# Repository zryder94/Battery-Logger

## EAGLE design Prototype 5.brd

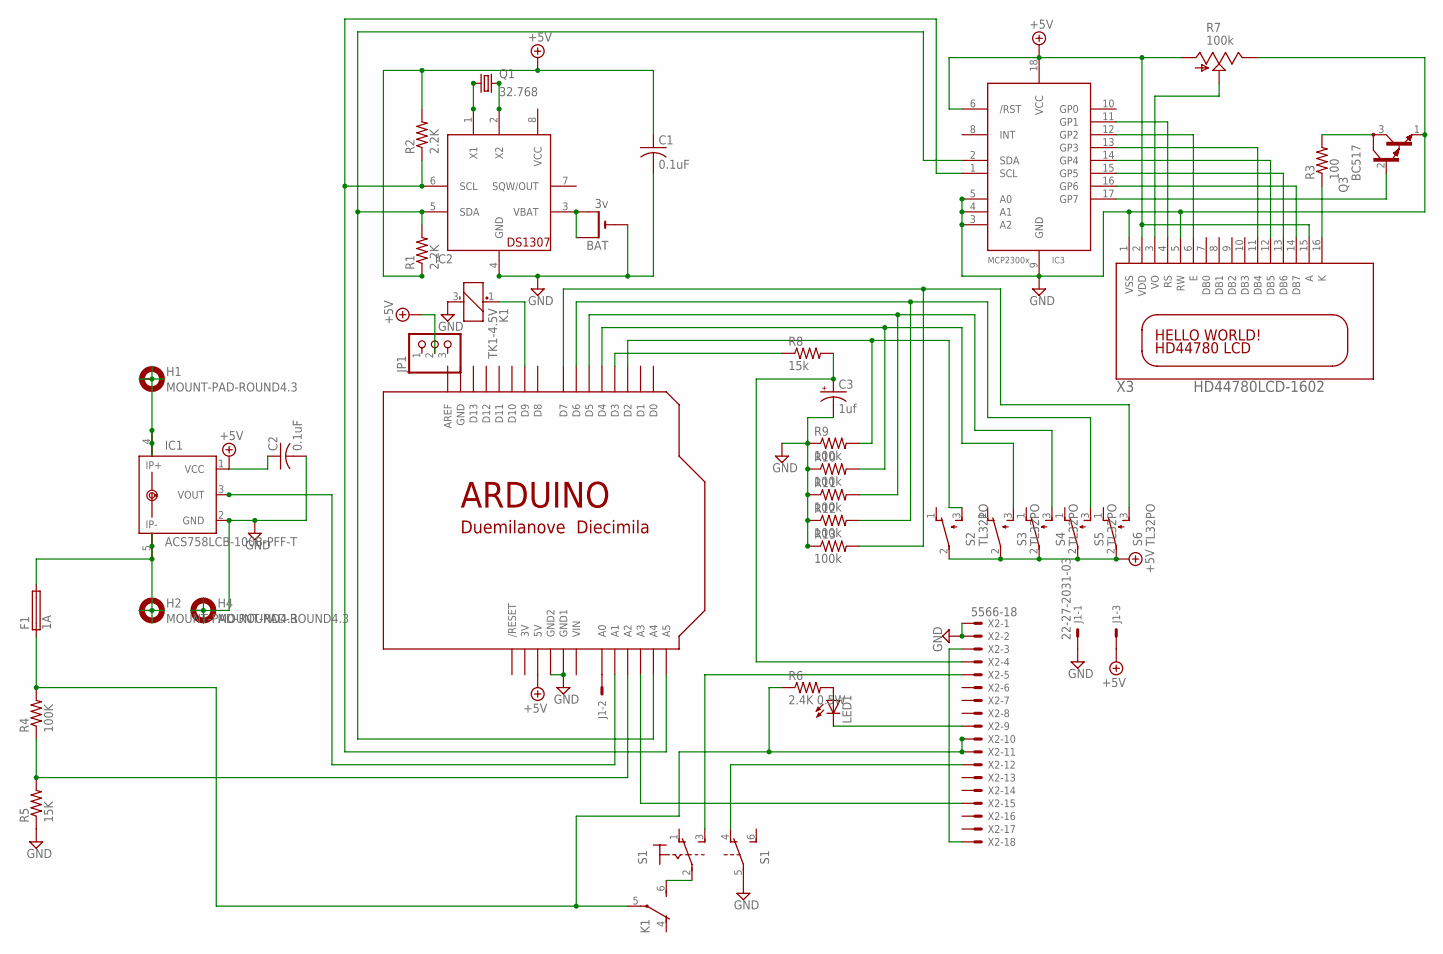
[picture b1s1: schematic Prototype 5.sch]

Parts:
BAT: 3v; CR1220-THM
C1, C2: 0.1uF; C050-024X044
C3: 1uf; E2,5-6E
F1: 1A; SH22,5
H1, H2, H4: MOUNT-PAD-ROUND4.3; 4,3-PAD
IC1: ACS758LCB-100B-PFF-T; CB-PFF
IC2: DS1307; DIL08
IC3: MCP2300X/P; DIL18
J1: 22-27-2031-03; 6410-03
JP1: PINHD-1X3; 1X03
K1: TK1-4.5V; TK
LED1: LED5MM
Q1: 32.768; TC38H
Q3: BC517; TO92
R1, R2: 2.2K; 0207/10
R3: 100; 0207/10
R4: 100K; 0207/10
R5: 15K; 0207/10
R6: 2.4K 0.5W; 0207/10
R7: 100k; B25U
R8: 15k; 0207/10
R9, R10, R11, R12, R13: 100k; 0207/10
S1: 320-938
S2, S3, S4, S5, S6: TL32PO; TL3XPO
U$1: ARDUINO-NOHOLE
X2: 5566-18
X3: HD44780LCD-1602; LCD1602

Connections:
3V: U$1.3V
24V: F1.2, H2.B4,3, IC1.5 (IP-), IC1.IP-1
+5V: C1.1, C2.1, IC1.1 (VCC), IC3.6 (/RST), IC3.18 (VCC), J1.3, JP1.2, R1.1, R2.2, R7.A, S2.2, S3.2, S4.2, S5.2, S6.2, U$1.5V, X3.2 (VDD), X3.15 (A)
GND: BAT.-, C1.2, C2.2, C3.-, H4.B4,3, IC1.2 (GND), IC2.4 (GND), IC3.3 (A2), IC3.4 (A1), IC3.5 (A0), IC3.9 (GND), J1.1, K1.3 (-), Q3.1 (E), R5.1, R7.E, R9.1, R10.1, R11.1, R12.1, R13.1, S1.5, U$1.GND, U$1.GND1, U$1.GND2, X2.1, X2.2, X3.1 (VSS), X3.5 (RW)
unnamed: IC2.1 (X1), Q1.1
unnamed: IC2.2 (X2), Q1.2
unnamed: C3.+, R8.2, X2.4
unnamed: BAT.+1 (+), BAT.+2 (+1), IC2.3 (VBAT)
unnamed: J1.2, U$1.A0
unnamed: IC1.3 (VOUT), U$1.A1
unnamed: IC2.6 (SCL), IC3.1 (SCL), R2.1, U$1.A5
unnamed: IC2.5 (SDA), IC3.2 (SDA), R1.2, U$1.A4
unnamed: H1.B4,3, IC1.4 (IP+), IC1.IP+1
unnamed: IC3.12 (GP2), X3.6 (E)
unnamed: IC3.11 (GP1), X3.4 (RS)
unnamed: R9.2, S2.3 (S), U$1.D2
unnamed: R10.2, S3.3 (S), U$1.D4
unnamed: S1.3 (S), X2.5
unnamed: K1.6 (S), S1.2
unnamed: LED1.K (C), X2.9
unnamed: R4.1, R5.2, U$1.A2
unnamed: S1.4 (O), X2.12
unnamed: K1.1 (+), U$1.D9
unnamed: R8.1, U$1.D3
unnamed: R13.2, S6.3 (S), U$1.D7
unnamed: IC3.17 (GP7), Q3.2 (B)
unnamed: IC3.13 (GP3), X3.11 (DB4)
unnamed: R3.1, X3.16 (K)
unnamed: Q3.3 (C), R3.2
unnamed: LED1.A, R6.2
unnamed: IC3.14 (GP4), X3.12 (DB5)
unnamed: U$1.A3, X2.15
unnamed: R11.2, S4.3 (S), U$1.D5
unnamed: X2.3, X2.18
unnamed: IC3.15 (GP5), X3.13 (DB6)
unnamed: F1.1, K1.5, R4.2, R6.1, X2.10, X2.11
unnamed: IC3.16 (GP6), X3.14 (DB7)
unnamed: R7.S, X3.3 (VO)
unnamed: R12.2, S5.3 (S), U$1.D6
VCC: IC2.8 (VCC)
VIN: U$1.VIN

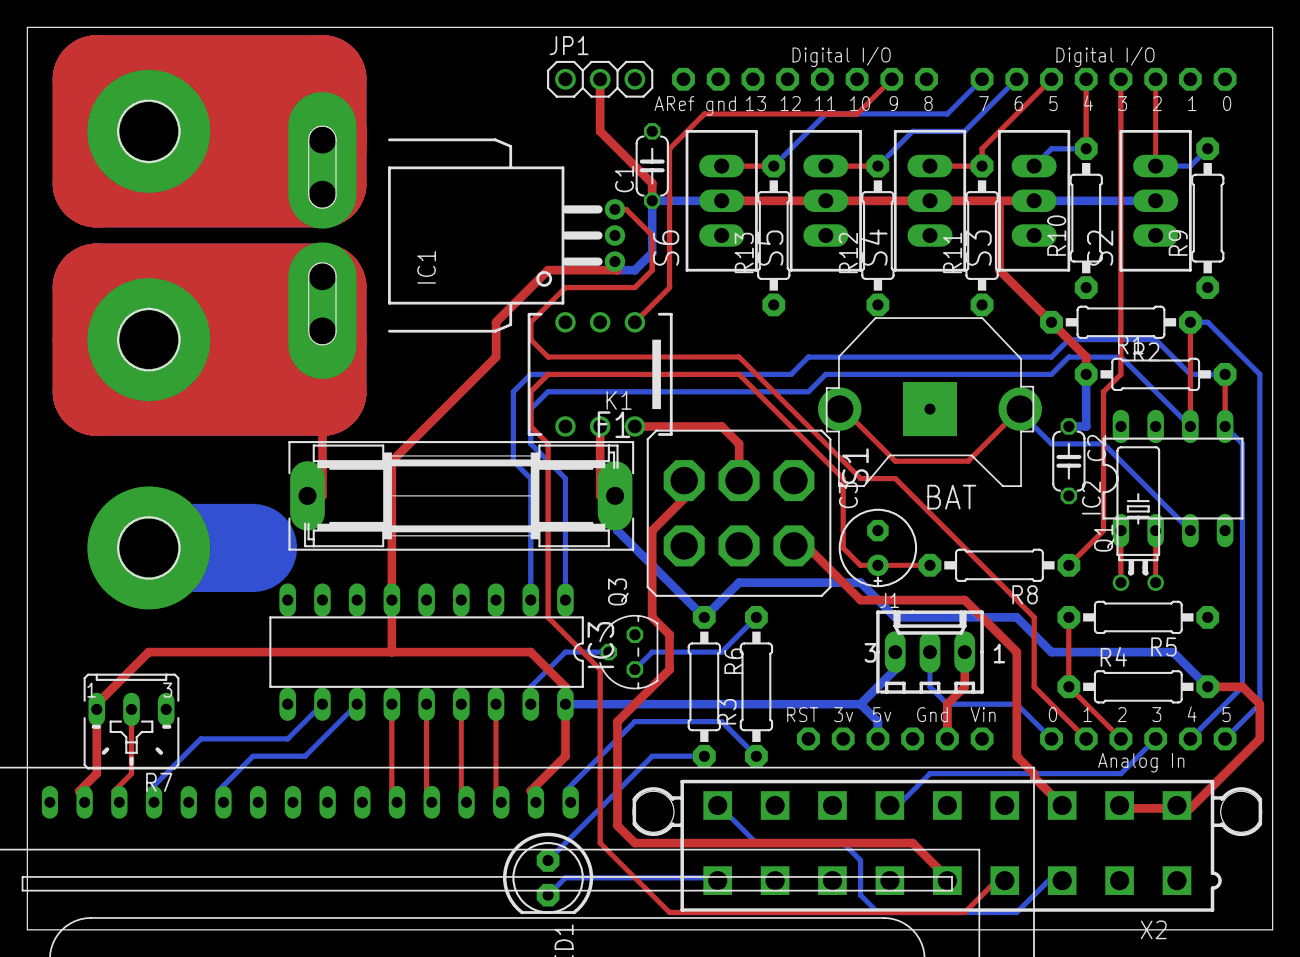
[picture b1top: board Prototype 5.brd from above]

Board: 2 copper layers, 91.1 x 66.0 mm, 39 parts (0 on the bottom side), 38 nets.

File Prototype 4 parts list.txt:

Partlist

Exported from Prototype 4.sch at 4/30/2012 8:23:52 AM

EAGLE Version 6.0.0 Copyright (c) 1988-2011 CadSoft

Assembly variant: 

Part     Value                Device               Package        Library        Sheet

BAT      3v                   CR1220THM            CR1220-THM     adafruit       1	3001K-ND
C1       0.1uF                C-US050-024X044      C050-024X044   adafruit       1	478-6008-ND
C2       0.1uF                C-US050-024X044      C050-024X044   adafruit       1	478-6008-ND
C3       1uf                  CPOL-USE2,5-6E       E2,5-6E        resistor       1	ECA-1HM010
F1       1A                   SH22,5               SH22,5         fuse           1	486-1258-ND
H1       MOUNT-PAD-ROUND4.3   MOUNT-PAD-ROUND4.3   4,3-PAD        holes          1
H2       MOUNT-PAD-ROUND4.3   MOUNT-PAD-ROUND4.3   4,3-PAD        holes          1
H4       MOUNT-PAD-ROUND4.3   MOUNT-PAD-ROUND4.3   4,3-PAD        holes          1
IC1      ACS758LCB-100B-PFF-T ACS758LCB-100B-PFF-T CB-PFF         allegro        1	620-1320-ND	40mV/A
IC2      DS1307               DS1307               DIL08          adafruit       1	DS1307+-ND
IC3      MCP2300X/P           MCP2300X/P           DIL18          adafruit       1	MCP23008-E/P-ND
J1       22-27-2031-03        22-27-2031-03        6410-03        con-molex      1	WM4201-ND
JP1                           PINHD-1X3            1X03           adafruit       1	A26509-40-ND
K1       TK1-4.5V             TK1-4.5V             TK             relay          1	255-1757-5-ND
LED1                          LED5MM               LED5MM         adafruit       1	C503B-RCN-CW0Z0AA1-ND
Q1       32.768               CRYSTALTC38H         TC38H          crystal        1	300-8763-ND
Q3       BC517                BC517                TO92           transistor-npn 1	BC517RL1GOSCT-ND
R1       2.2K                 R-US_0207/10         0207/10        adafruit       1	2.2KH-ND
R2       2.2K                 R-US_0207/10         0207/10        adafruit       1	2.2KH-ND
R3       100                  R-US_0207/10         0207/10        adafruit       1	100H-ND
R4       100K                 R-US_0207/10         0207/10        adafruit       1	100KADCT-ND
R5       15K                  R-US_0207/10         0207/10        adafruit       1	15KADCT-ND
R6       2.4K 0.5W            R-US_0207/10         0207/10        adafruit       1	2.4KH-ND
R7       100k                 TRIM_US-B25U         B25U           pot            1	3362U-104LF-ND
R8       15k                  R-US_0207/10         0207/10        adafruit       1	15KH-ND
R9       100k                 R-US_0207/10         0207/10        adafruit       1	100KH-ND
R10      100k                 R-US_0207/10         0207/10        adafruit       1	100KH-ND
R11      100k                 R-US_0207/10         0207/10        adafruit       1	100KH-ND
R12      100k                 R-US_0207/10         0207/10        adafruit       1	100KH-ND
R13      100k                 R-US_0207/10         0207/10        adafruit       1	100KH-ND
S1                            320-938              320-938        switch         1	A201P3ZQ04-ND
S2       TL32PO               TL32PO               TL3XPO         switch         1	SW630-ND
S3       TL32PO               TL32PO               TL3XPO         switch         1	SW630-ND
S4       TL32PO               TL32PO               TL3XPO         switch         1	SW630-ND
S5       TL32PO               TL32PO               TL3XPO         switch         1	SW630-ND
S6       TL32PO               TL32PO               TL3XPO         switch         1	SW630-ND
U$1      ARDUINO-NOHOLE       ARDUINO-NOHOLE       ARDUINO-NOHOLE adafruit       1
X2       5566-18              5566-18              5566-18        con-molex      1	WM3883-ND
X3       HD44780LCD-1602      HD44780LCD-1602      LCD1602        adafruitedit   1
				8 pin IC Socket						3M5473-ND
				18 pin IC Socket					3M5464-ND
				Resistor mounting kit					K3003-ND


5v non-latching relay 255-1028-5-ND
4.5v non-latching relay 255-1757-5-ND

pushbutton switches SW630-ND

Resistor mounting kit	K3003-ND


Index	Quantity	Part Number	Description	Customer Reference	Backorder Quantity	Unit Price	Extended Price
1	2	K3003-ND	MOUNTING KIT FOR FSE 1000		0	14.28000	$28.56
2	1	3001K-ND	HOLDER BATTERY COIN 12MM DIA THM		0	0.57000	$0.57
3	10	478-6008-ND	CAP CER 0.1UF 50V 5% RADIAL		0	0.41000	$4.10
4	2	P5174-ND	CAP ALUM 1UF 50V 20% RADIAL		0	0.20000	$0.40
5	1	486-1258-ND	FUSEHOLDER 22.5MM PCB 5X20MM BK		0	0.67000	$0.67
6	1	620-1320-ND	SENSOR CURRENT 50A 5V BI 5-CB		0	7.00000	$7.00
7	1	DS1307+-ND	IC RTC SERIAL 512K 8-DIP		0	3.81000	$3.81
8	1	MCP23008-E/P-ND	IC I/O EXPANDER I2C 8B 18DIP		0	1.22000	$1.22
9	3	WM4201-ND	CONN HEADER 3POS .100 VERT TIN		0	0.56000	$1.68
10	2	A26509-40-ND	CONN HDR BRKWAY .100 40POS VERT		0	1.90000	$3.80
11	1	255-1757-5-ND	RELAY GEN PURPOSE SPDT 2A 4.5V		0	5.29000	$5.29
12	10	C503B-RCN-CW0Z0AA1-ND	LED 5MM RED CLEAR 624NM 30DEG		0	0.14000	$1.40
13	2	300-8763-ND	CRYSTAL 32.768 KHZ 12.5PF CYL		0	0.70000	$1.40
14	2	BC517RL1GOSCT-ND	TRANS DARL NPN 30V 1A TO-92		0	0.56000	$1.12
15	10	2.2KH-ND	RES 2.2K OHM 1/2W 5% CARBON FILM		0	0.08300	$0.83
16	5	100H-ND	RES 100 OHM 1/2W 5% CARBON FILM		0	0.10000	$0.50
17	2	100KADCT-ND	RES 100K OHM 1/4W 0.1% MF AXL		0	0.55000	$1.10
18	2	15KADCT-ND	RES 15K OHM 1/4W 0.1% MF AXL		0	0.55000	$1.10
19	10	2.4KH-ND	RES 2.4K OHM 1/2W 5% CARBON FILM		0	0.08300	$0.83
20	2	3362U-104LF-ND	TRIMMER 100K OHM 0.5W TH		0	1.05000	$2.10
21	10	15KH-ND	RES 15K OHM 1/2W 5% CARBON FILM		0	0.08300	$0.83
22	2	A201P3ZQ04-ND	SWITCH TOGGLE DPDT WIRE LUG SLV		0	4.10000	$8.20
23	5	SW630-ND	SWITCH PUSH SPST-NO 3A 125V		0	1.81000	$9.05
24	1	WM3883-ND	CONN HEADER 18POS 4.2MM VERT TIN		0	3.09000	$3.09
25	2	3M5473-ND	SOCKET IC OPEN FRAME 8POS .3"		0	0.29000	$0.58
26	2	3M5464-ND	SOCKET IC OPEN FRAME 18POS .3"		0	0.30000	$0.60
27	10	S100KHCT-ND	RES 100K OHM 1/2W 5% CF MINI		0	0.07800	$0.78
Subtotal	$90.61






















Current Sensor parts

Index	Quantity	Part Number	Description	Customer Reference	Backorder Quantity	Unit Price	Extended Price
1	1	620-1353-ND	IC SENSOR CURRENT 50A UNI 3-CB		0	7.00000	$7.00
2	10	100KADCT-ND	RES 100K OHM 1/4W 0.1% MF AXL		0	0.43700	$4.37
3	10	15KADCT-ND	RES 15K OHM 1/4W 0.1% MF AXL		0	0.43700	$4.37
4	5	478-6008-ND	CAP CER 0.1UF 50V 5% RADIAL		0	0.58000	$2.90
5	2	TIP102-BP-ND	TRANSISTOR NPN 8A 100V TO-220		0	1.40000	$2.80
6	1	255-1764-5-ND	RELAY LATCH LOPRO 2A 5VDC PCB		0	5.81000	$5.81
7	2	WM23708-ND	CONN RECEPT 18POS DUAL		0	1.71000	$3.42
8	1	WM3883-ND	CONN HEADER 18POS 4.2MM VERT TIN		0	3.17000	$3.17
9	40	WM3118CT-ND	CONN TERM FEMALE 16AWG TIN		0	0.31200	$12.48
10	2	PC40P-ND	PCB COPPER CLAD POS 3X4.5"2 SIDE		0	8.01000	$16.02
11	1	A201P3ZQ04-ND	SWITCH TOGGLE DPDT WIRE LUG SLV		0	4.03000	$4.03
12	1	3362U-104LF-ND	TRIMMER 100K OHM 0.5W TH		0	1.05000	$1.05
13	2	987-1311-ND	POT ROTARY 5K OHM 16MM SOLDER		0	0.76000	$1.52
14	1	DS1307+-ND	IC RTC SERIAL 512K 8-DIP		0	4.23000	$4.23
15	2	486-1258-ND	FUSEHOLDER 22.5MM PCB 5X20MM BK		0	0.64000	$1.28
16	1	CP-102A-ND	CONN JACK POWER 2.1MM PCB		0	0.92000	$0.92
17	10	C503B-RCN-CW0Z0AA1-ND	LED 5MM RED CLEAR 624NM 30DEG		0	0.14000	$1.40
18	1	300-8763-ND	CRYSTAL 32.768 KHZ 12.5PF CYL		0	0.70000	$0.70
19	5	2.4KH-ND	RES 2.4K OHM 1/2W 5% CARBON FILM		0	0.12800	$0.64
20	5	2.2KH-ND	RES 2.2K OHM 1/2W 5% CARBON FILM		0	0.12800	$0.64
21	1	3001K-ND	HOLDER BATTERY COIN 12MM DIA THM		0	0.68000	$0.68
22	1	P033-ND	BATTERY LITHIUM COIN 3V 12.5MM		0	0.95000	$0.95
23	1	A26509-40-ND	CONN HDR BRKWAY .100 40POS VERT		0	1.76000	$1.76
24	1	3M5473-ND	SOCKET IC OPEN FRAME 8POS .3"		0	0.54000	$0.54
Subtotal	$82.68
Shipping	Estimate
Sales Tax	$5.89
Total	unknown

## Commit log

2012-05-02 Initial upload of my code for the next charger logger, with buttons!
2012-05-02 Added the board, schematic, and parts list.
2012-05-10 Uploaded the testing code, and the revised board schematics.
